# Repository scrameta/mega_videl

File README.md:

# mega_videl

- 1GB 32-bit wide DDR3 ram running at 400MHz
- Cyclone V GX FPGA
- DVI + audio output up to 300MHz (4K30)
- Falcon audio intercept + modify
- High speed link to future expansion (Plan: System ram board)
- PCIe 1x
- USB2
- Ethernet

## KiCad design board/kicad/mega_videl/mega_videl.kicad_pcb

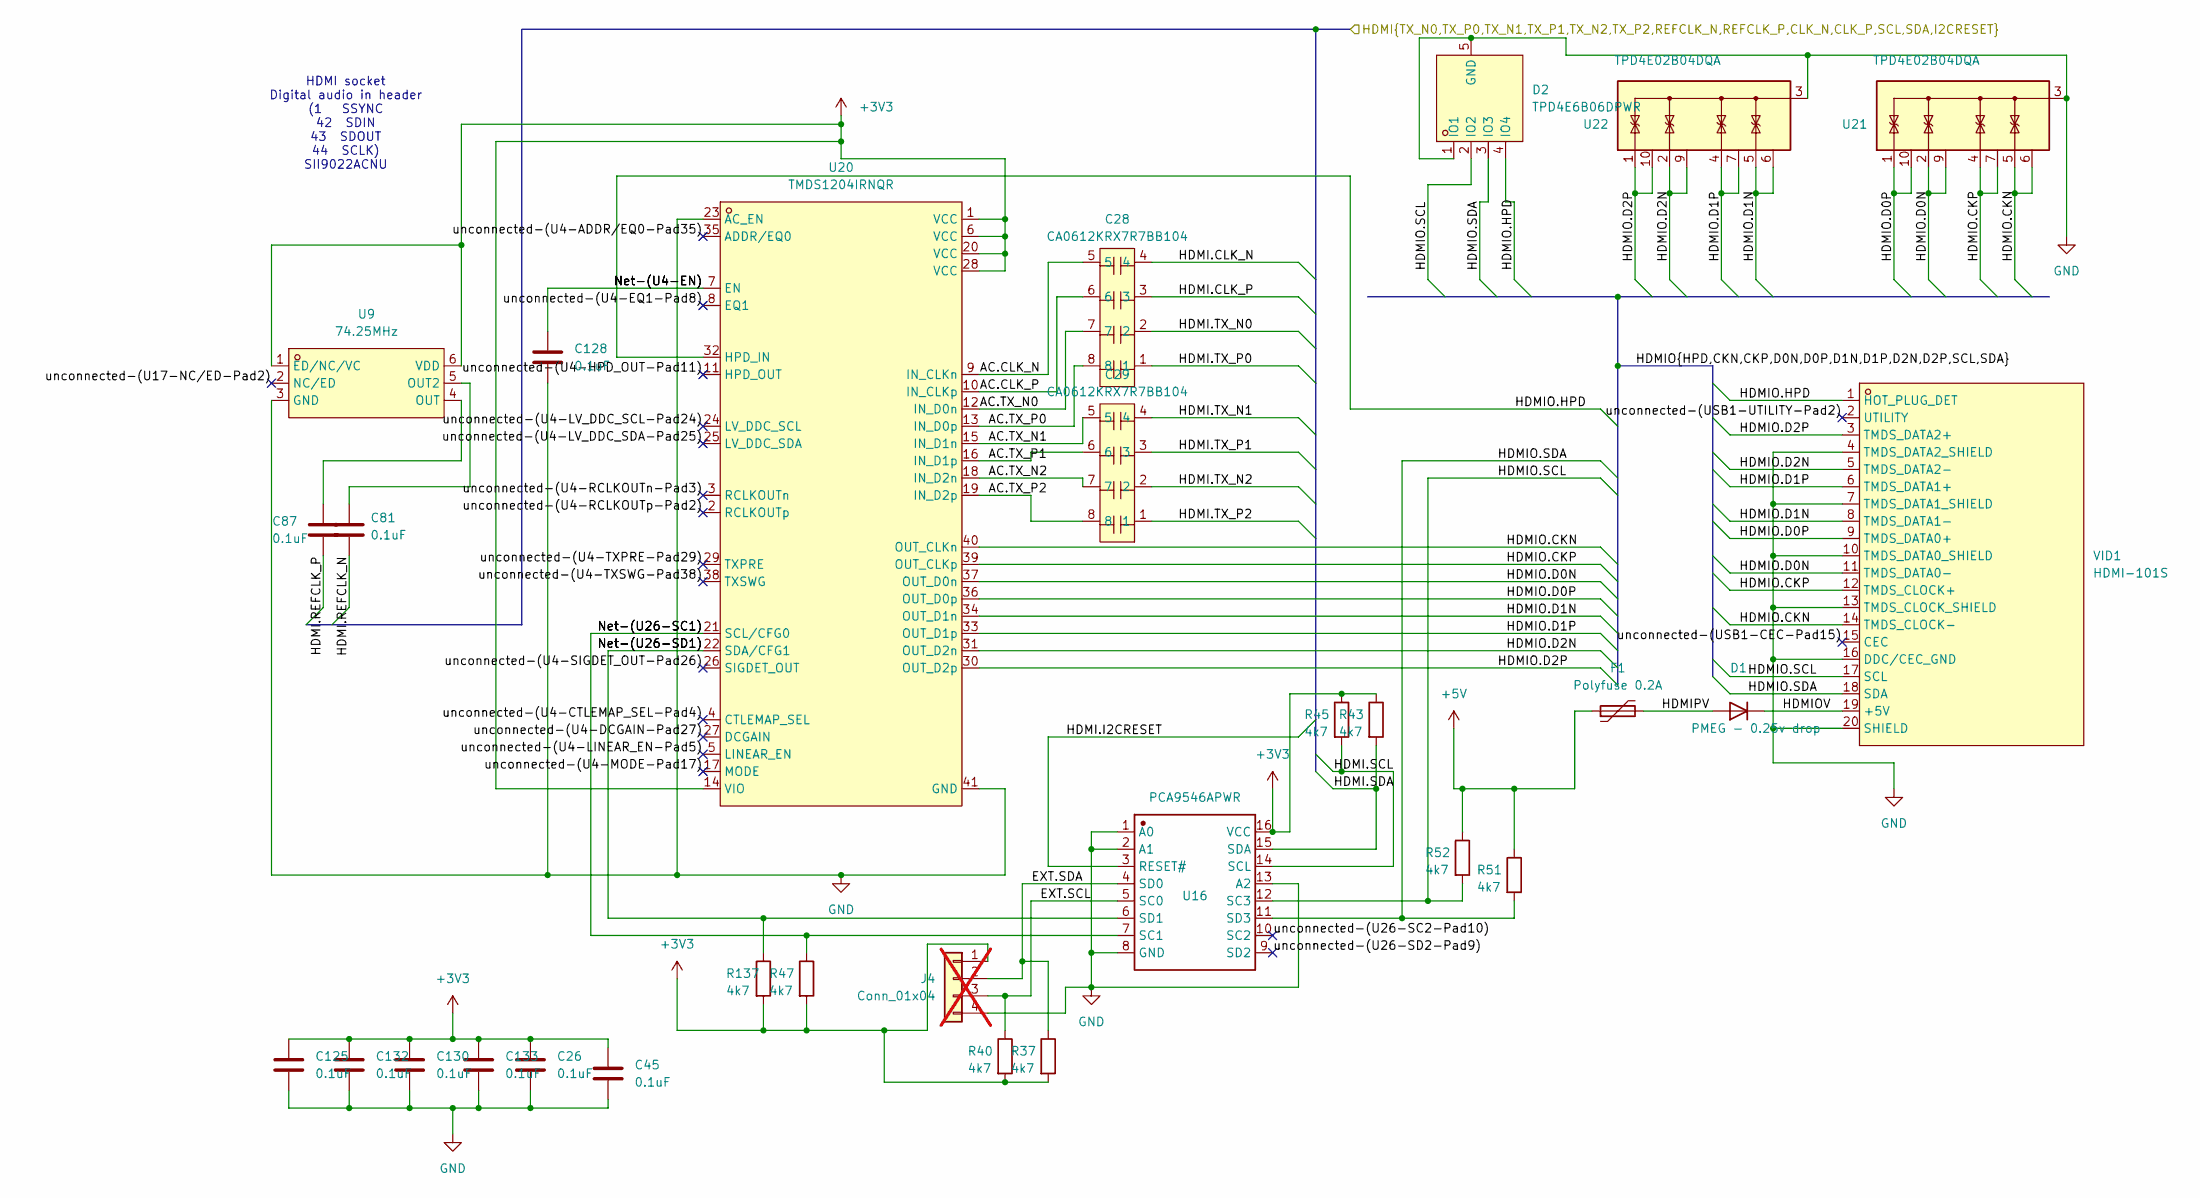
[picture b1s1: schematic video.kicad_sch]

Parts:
C26, C45, C125, C132: 0.1uF; C_0603_1608Metric; LCSC C14663
C28, C29: CA0612KRX7R7BB104; CAP-ARRAY-SMD_0612-8P-L3.2-W1.6-BL; MPN CA0612KRX7R7BB104; LCSC Part C576639
C81, C87, C128, C130, C133: 0.1uF; C_0402_1005Metric; LCSC C1525
D1: PMEG - 0.25v drop; D_SOD-323; LCSC C7420331
D2: TPD4E6B06DPWR; X2SON-4_L0.8-W0.8-P0.48-TL-A; MPN TPD4E6B06DPWR; LCSC Part C2869397
F1: Polyfuse 0.2A; R_0603_1608Metric; LCSC C207011
J4: Conn_01x04; PinHeader_1x04_P2.54mm_Vertical; not fitted
R37, R40, R43, R45, R47, R51, R52, R137: 4k7; R_0603_1608Metric; LCSC C23162
U9: 74.25MHz; OSC-SMD_6P-L3.2-W2.5-BL_RENESAS_XLH3XXXXXXXXXX; MPN SiT9121AC-2B2-33E74.250000; LCSC Part C836732
U16: PCA9546APWR; TSSOP-16_L5.0-W4.4-P0.65-LS6.4-BL; Manufacturer Part PCA9546APWR; JLC_3DModel 534f03d8fe164fbab551f91e5a792e30
U20: TMDS1204IRNQR; WQFN-40_L6.0-W4.0-P0.40-TL-EP4.7; MPN TMDS1204IRNQR; LCSC Part C19272424
U21, U22: TPD4E02B04DQA; USON-10_2.5x1.0mm_P0.5mm; LCSC C106794
VID1: HDMI-101S; HDMI-SMD_HDMI-101S; MPN HDMI-101S; LCSC Part C720620

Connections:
+3V3: C26.1, C45.1, C125.1, C130.1, C132.1, C133.1, J4.1, R37.2, R40.2, R43.1, R45.1, R47.2, R137.2, U9.1 (ED/NC/VC), U9.6 (VDD), U16.16 (VCC), U20.1 (VCC), U20.6 (VCC), U20.14 (VIO), U20.20 (VCC), U20.28 (VCC); also elsewhere on the board
+5V: F1.1, R51.1, R52.1; also elsewhere on the board
/fpga/HDMI.CLK_N: C28.4; also elsewhere on the board
/fpga/HDMI.CLK_P: C28.3; also elsewhere on the board
/fpga/HDMI.I2CRESET: U16.3 (RESET#); also elsewhere on the board
/fpga/HDMI.REFCLK_N: C81.1; also elsewhere on the board
/fpga/HDMI.REFCLK_P: C87.1; also elsewhere on the board
/fpga/HDMI.SCL: R45.2, U16.14 (SCL); also elsewhere on the board
/fpga/HDMI.SDA: R43.2, U16.15 (SDA); also elsewhere on the board
/fpga/HDMI.TX_N0: C28.2; also elsewhere on the board
/fpga/HDMI.TX_N1: C29.4; also elsewhere on the board
/fpga/HDMI.TX_N2: C29.2; also elsewhere on the board
/fpga/HDMI.TX_P0: C28.1; also elsewhere on the board
/fpga/HDMI.TX_P1: C29.3; also elsewhere on the board
/fpga/HDMI.TX_P2: C29.1; also elsewhere on the board
/video/AC.CLK_N: C28.5, U20.9 (IN_CLKn)
/video/AC.CLK_P: C28.6, U20.10 (IN_CLKp)
/video/AC.TX_N0: C28.7, U20.12 (IN_D0n)
/video/AC.TX_N1: C29.5, U20.15 (IN_D1n)
/video/AC.TX_N2: C29.7, U20.18 (IN_D2n)
/video/AC.TX_P0: C28.8, U20.13 (IN_D0p)
/video/AC.TX_P1: C29.6, U20.16 (IN_D1p)
/video/AC.TX_P2: C29.8, U20.19 (IN_D2p)
/video/EXT.SCL: J4.3, R40.1, U16.5 (SC0)
/video/EXT.SDA: J4.2, R37.1, U16.4 (SD0)
/video/HDMIO.CKN: U20.40 (OUT_CLKn), U21.5 (IO4), U21.6 (NC), VID1.14 (TMDS_CLOCK-)
/video/HDMIO.CKP: U20.39 (OUT_CLKp), U21.4 (IO3), U21.7 (NC), VID1.12 (TMDS_CLOCK+)
/video/HDMIO.D0N: U20.37 (OUT_D0n), U21.2 (IO2), U21.9 (NC), VID1.11 (TMDS_DATA0-)
/video/HDMIO.D0P: U20.36 (OUT_D0p), U21.1 (IO1), U21.10 (NC), VID1.9 (TMDS_DATA0+)
/video/HDMIO.D1N: U20.34 (OUT_D1n), U22.5 (IO4), U22.6 (NC), VID1.8 (TMDS_DATA1-)
/video/HDMIO.D1P: U20.33 (OUT_D1p), U22.4 (IO3), U22.7 (NC), VID1.6 (TMDS_DATA1+)
/video/HDMIO.D2N: U20.31 (OUT_D2n), U22.2 (IO2), U22.9 (NC), VID1.5 (TMDS_DATA2-)
/video/HDMIO.D2P: U20.30 (OUT_D2p), U22.1 (IO1), U22.10 (NC), VID1.3 (TMDS_DATA2+)
/video/HDMIO.HPD: D2.4 (IO4), U20.32 (HPD_IN), VID1.1 (HOT_PLUG_DET)
/video/HDMIO.SCL: D2.2 (IO2), R52.2, U16.12 (SC3), VID1.17 (SCL)
/video/HDMIO.SDA: D2.3 (IO3), R51.2, U16.11 (SD3), VID1.18 (SDA)
/video/HDMIOV: D1.1 (K), VID1.19 (+5V)
/video/HDMIPV: D1.2 (A), F1.2
/video/Net-(U4-EN): C128.1, U20.7 (EN)
/video/Net-(U26-SC1): R47.1, U16.7 (SC1), U20.21 (SCL/CFG0)
/video/Net-(U26-SD1): R137.1, U16.6 (SD1), U20.22 (SDA/CFG1)
/video/unconnected-(U4-ADDR/EQ0-Pad35): U20.35 (ADDR/EQ0)
/video/unconnected-(U4-CTLEMAP_SEL-Pad4): U20.4 (CTLEMAP_SEL)
/video/unconnected-(U4-DCGAIN-Pad27): U20.27 (DCGAIN)
/video/unconnected-(U4-EQ1-Pad8): U20.8 (EQ1)
/video/unconnected-(U4-HPD_OUT-Pad11): U20.11 (HPD_OUT)
/video/unconnected-(U4-LINEAR_EN-Pad5): U20.5 (LINEAR_EN)
/video/unconnected-(U4-LV_DDC_SCL-Pad24): U20.24 (LV_DDC_SCL)
/video/unconnected-(U4-LV_DDC_SDA-Pad25): U20.25 (LV_DDC_SDA)
/video/unconnected-(U4-MODE-Pad17): U20.17 (MODE)
/video/unconnected-(U4-RCLKOUTn-Pad3): U20.3 (RCLKOUTn)
/video/unconnected-(U4-RCLKOUTp-Pad2): U20.2 (RCLKOUTp)
/video/unconnected-(U4-SIGDET_OUT-Pad26): U20.26 (SIGDET_OUT)
/video/unconnected-(U4-TXPRE-Pad29): U20.29 (TXPRE)
/video/unconnected-(U4-TXSWG-Pad38): U20.38 (TXSWG)
/video/unconnected-(U17-NC/ED-Pad2): U9.2 (NC/ED)
/video/unconnected-(U26-SC2-Pad10): U16.10 (SC2)
/video/unconnected-(U26-SD2-Pad9): U16.9 (SD2)
/video/unconnected-(USB1-CEC-Pad15): VID1.15 (CEC)
/video/unconnected-(USB1-UTILITY-Pad2): VID1.2 (UTILITY)
GND: C26.2, C45.2, C125.2, C128.2, C130.2, C132.2, C133.2, D2.1 (IO1), D2.5 (GND), J4.4, U9.3 (GND), U16.1 (A0), U16.2 (A1), U16.8 (GND), U16.13 (A2), U20.23 (AC_EN), U20.41 (GND), U21.3 (G), U21.8 (G), U22.3 (G), U22.8 (G), VID1.4 (TMDS_DATA2_SHIELD), VID1.7 (TMDS_DATA1_SHIELD), VID1.10 (TMDS_DATA0_SHIELD), VID1.13 (TMDS_CLOCK_SHIELD), VID1.16 (DDC/CEC_GND), VID1.20 (SHIELD); also elsewhere on the board
unnamed: C81.2, U9.5 (OUT2)
unnamed: C87.2, U9.4 (OUT)

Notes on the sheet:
HDMI socket Digital audio in header (1 SSYNC 42 SDIN 43 SDOUT 44 SCLK) SII9022ACNU

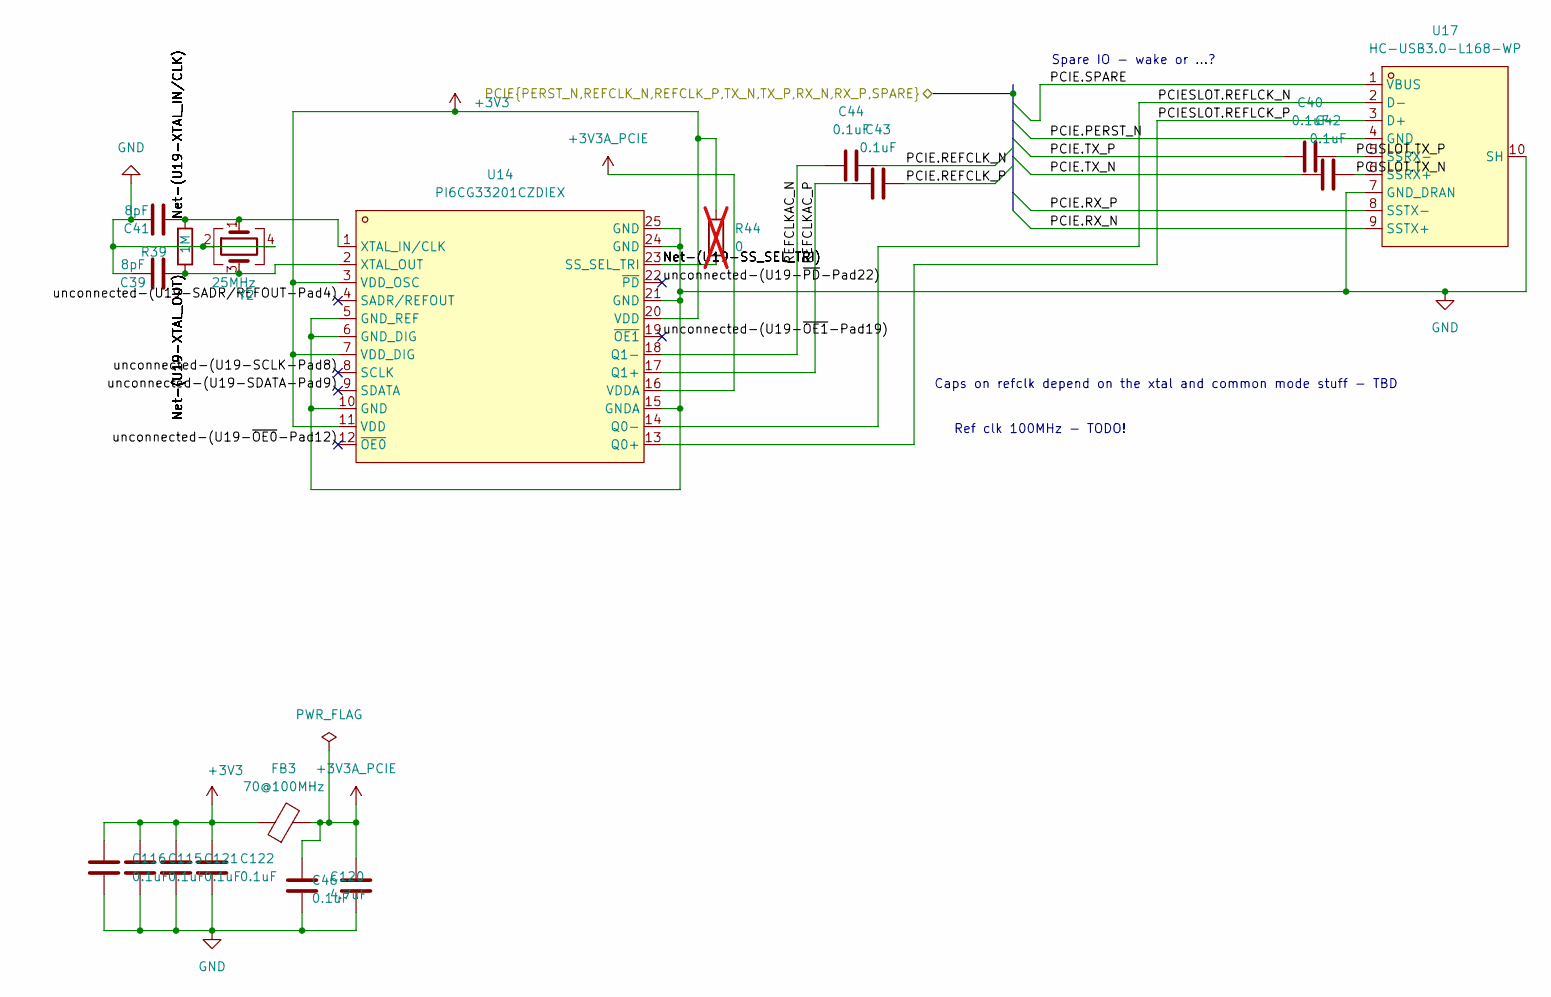
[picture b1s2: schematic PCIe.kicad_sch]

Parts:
C39, C41: 8pF; C_0603_1608Metric; LCSC C327316
C40, C42, C43, C44: 0.1uF; C_0603_1608Metric; LCSC C14663
C46, C115, C116, C121, C122: 0.1uF; C_0402_1005Metric; LCSC C1525
C120: 4.7uF; C_0805_2012Metric; LCSC C1779
FB3: 70@100MHz; L_0805_2012Metric; LCSC C85840
R39: 1M; R_0603_1608Metric; LCSC C22935
R44: 0; R_0603_1608Metric; LCSC C21189; not fitted
U14: PI6CG33201CZDIEX; TQFN-24_L4.0-W4.0-P0.50-TL-EP2.8; MPN PI6CG33201CZDIEX; LCSC Part C1236517
U17: HC-USB3.0-L168-WP; USB-TH_USB3.0-A; MPN HC-USB3.0-L168-WP; LCSC Part C7501850
Y2: 25MHz; Crystal_SMD_3225-4Pin_3.2x2.5mm; LCSC C5742221

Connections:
+3V3: C115.1, C116.1, C121.1, C122.1, FB3.1, R44.1, U14.3 (VDD_OSC), U14.7 (VDD_DIG), U14.11 (VDD), U14.20 (VDD); also elsewhere on the board
+3V3A_PCIE: C46.1, C120.1, FB3.2, U14.16 (VDDA)
/PCIe/Net-(U19-SS_SEL_TRI): R44.2, U14.23 (SS_SEL_TRI)
/PCIe/Net-(U19-XTAL_IN/CLK): C41.2, R39.2, U14.1 (XTAL_IN/CLK), Y2.1
/PCIe/Net-(U19-XTAL_OUT): C39.2, R39.1, U14.2 (XTAL_OUT), Y2.3
/PCIe/PCIESLOT.REFLCK_N: U14.14 (Q0-), U17.2 (D-)
/PCIe/PCIESLOT.REFLCK_P: U14.13 (Q0+), U17.3 (D+)
/PCIe/PCISLOT.TX_N: C42.2, U17.6 (SSRX+)
/PCIe/PCISLOT.TX_P: C40.2, U17.5 (SSRX-)
/PCIe/REFCLKAC_N: C44.1, U14.18 (Q1-)
/PCIe/REFCLKAC_P: C43.1, U14.17 (Q1+)
/PCIe/unconnected-(U19-SADR/REFOUT-Pad4): U14.4 (SADR/REFOUT)
/PCIe/unconnected-(U19-SCLK-Pad8): U14.8 (SCLK)
/PCIe/unconnected-(U19-SDATA-Pad9): U14.9 (SDATA)
/PCIe/unconnected-(U19-~OE0-Pad12): U14.12 (~OE0)
/PCIe/unconnected-(U19-~OE1-Pad19): U14.19 (~OE1)
/PCIe/unconnected-(U19-~PD-Pad22): U14.22 (~PD)
/fpga/PCIE.PERST_N: U17.4 (GND); also elsewhere on the board
/fpga/PCIE.REFCLK_N: C44.2; also elsewhere on the board
/fpga/PCIE.REFCLK_P: C43.2; also elsewhere on the board
/fpga/PCIE.RX_N: U17.9 (SSTX+); also elsewhere on the board
/fpga/PCIE.RX_P: U17.8 (SSTX-); also elsewhere on the board
/fpga/PCIE.SPARE: U17.1 (VBUS); also elsewhere on the board
/fpga/PCIE.TX_N: C42.1; also elsewhere on the board
/fpga/PCIE.TX_P: C40.1; also elsewhere on the board
GND: C39.1, C41.1, C46.2, C115.2, C116.2, C120.2, C121.2, C122.2, U14.5 (GND_REF), U14.6 (GND_DIG), U14.10 (GND), U14.15 (GNDA), U14.21 (GND), U14.24 (GND), U14.25 (GND), U17.7 (GND_DRAN), U17.10 (SH), Y2.2, Y2.4; also elsewhere on the board

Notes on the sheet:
Caps on refclk depend on the xtal and common mode stuff - TBD
Spare IO - wake or ...?
Ref clk 100MHz - TODO!
